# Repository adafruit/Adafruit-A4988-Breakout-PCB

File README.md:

## Adafruit A4988 Stepper Motor Driver Breakout Board PCB

<a href="http://www.adafruit.com/products/6109"><br/>
Click here to purchase one from the Adafruit shop</a>

PCB files for the Adafruit A4988 Stepper Motor Driver Breakout Board. 

Format is EagleCAD schematic and board layout
* https://www.adafruit.com/product/6109

### Description

Stepper motors are used for CNC machines, 3D printers, and whenever else one needs precise, powerful motion. But to get good behavior from steppers you need a motor driver chip that can provide high bursts of current, and for smooth motion, be able to PWM that current for microstepping support. You can DIY this with a lot of timers, a microcontroller and an  H-Bridge chip - or you could take the easy way out and use an Adafruit A4988 Stepper Motor Driver Breakout Board which makes controlling stepper motors easy-breezy.

All you need is two output pins, no timers, PWM or real-time microcontroller. Set the DIRection pin high or low to set the spin orientation. Then toggle the STEP pin to take one step or microstep at a time. You can set whether you want to go fast with single-step mode or improve the motion precise with 1/4, 1/8 or 1/16 microstepping per STEP toggle. By default the driver is set to 1/16 microstep mode, you can change it by tying the MS1/MS2/MS3 pins low, either with jumpers or with 3 more output pins. The step/microstep mode can even be adjusted on the fly! LEDs on the DIR and STEP pins let you get visual feedback of your motor signal.

The Allegro A4988 is a popular driver chip, with small breakout boards used in many 3D printers. Those breakouts are great for plugging into motherboards, but are a little tough to use for prototyping. Our version comes with terminal blocks for the motor power and stepper wires, plus nicely labeled pins for control and mounting holes.

We fabricated the board with 2 oz copper to give it a hand with the 2A-max current that this driver can handle. To use the current limiting capability, twist the onboard potentiometer: when all the way to the right we can get to up to 2A max. Note that the higher the currents will heat up both the motor driver and stepper so you may need to add heatsinking to the chip. We don't include a heatsink but you can get a tall ~80ºC/W or short ~90ºC/W heatsink to attach on top.

Features:

* Allegro A4988 DMOS microstepping driver with translator and overcurrent protection
* Motor voltage from 8V to 35VDC
* Vdd/Logic voltage from 3V to 5V, use with anything from an Arduino-compatible or ESP32 to Raspberry Pi other Single Board Computer
* Terminal screw block connections for easy VMotor power and 4-wire bi-polar stepper motor connection with 26-20AWG slots, 2.54mm / 0.1" spacing
* Control steppers using only two pins: DIRection and STEP
* Defaults to 1/16 microstep mode, change by grounding MS1/MS2/MS3 pins (see A4988 datasheet for pin configuration)
* Red and Green LEDs on DIR signal to let you know forward or backward motion
* Yellow LED on STEP to let you know that motor driver is being moved
* Sleep, Reset and Enable control lines for low power / deactivation
* Potentiometer to set current limiting, up to 2A
* 22uF 50V electrolytic capacitor on motor power
* 2 Oz copper for better current carrying and heatsinking
* Four mounting holes

Comes as one assembled and tested breakout plus a small strip of header. You'll need to do some light soldering to attach the header onto the breakout PCB. Microcontroller, motors, and power supply not included. You will need some sort of driver board that will toggle the DIR/STEP pins for you.

### License

Adafruit invests time and resources providing this open source design, please support Adafruit and open-source hardware by purchasing products from [Adafruit](https://www.adafruit.com)!

Designed by Limor Fried/Ladyada for Adafruit Industries.

Creative Commons Attribution/Share-Alike, all text above must be included in any redistribution. 
See license.txt for additional details.

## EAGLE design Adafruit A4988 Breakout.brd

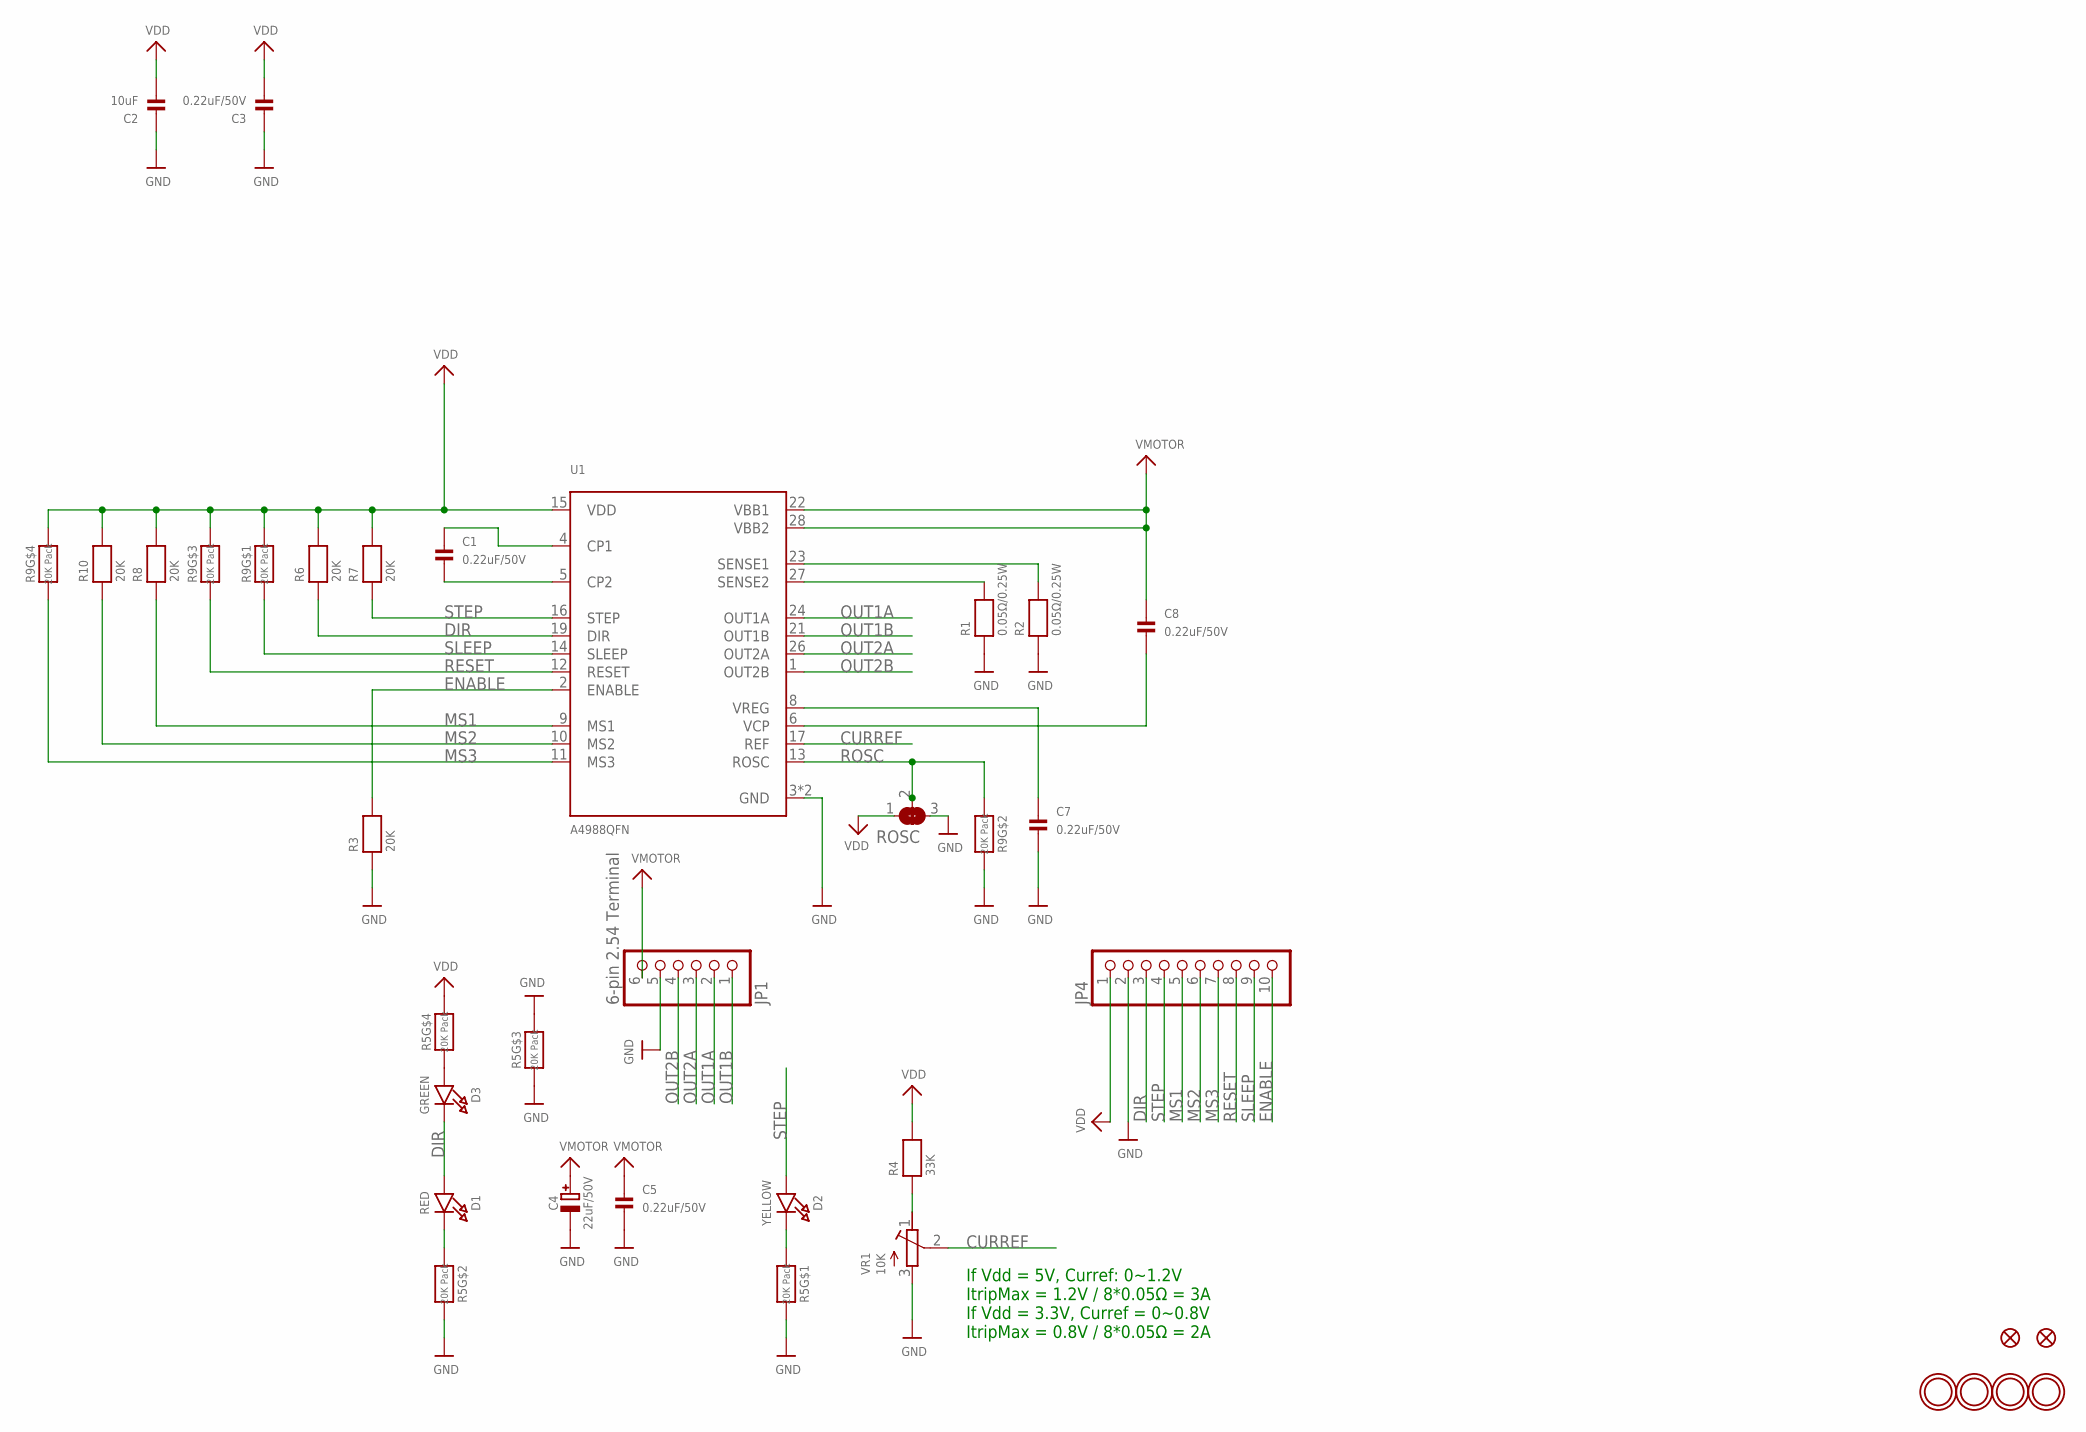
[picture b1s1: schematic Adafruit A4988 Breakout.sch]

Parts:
C1, C3, C5, C7, C8: 0.22uF/50V; 0603-NO
C2: 10uF; 0805-NO
C4: 22uF/50V; PANASONIC_C
D1: RED; CHIPLED_0603_NOOUTLINE
D2: YELLOW; CHIPLED_0603_NOOUTLINE
D3: GREEN; CHIPLED_0603_NOOUTLINE
JP1: 6-pin 2.54 Terminal; 1X06_2.54MMTERMINAL
JP4: HEADER-1X1070MIL; 1X10_ROUND70
R1, R2: 0.05Ω/0.25W; 0603-NO
R3, R6, R7, R8, R10: 20K; 0603-NO
R4: 33K; 0603-NO
R5, R9: 20K Pack; RESPACK_4X0603
ROSC: SOLDERJUMPER_2WAY; SOLDERJUMPER_2WAY_OPEN_NOPASTE
U1: A4988QFN; QFN28_5MM
U$10, U$11: FIDUCIAL_0.5MM
U$18, U$22, U$26, U$27: MOUNTINGHOLE2.0; MOUNTINGHOLE_2.0_PLATED
VR1: 10K; RTRIM3314J

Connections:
CURREF: U1.17 (REF), VR1.2 (S)
DIR: D1.A, D3.C, JP4.3, R6.1, U1.19 (DIR)
ENABLE: JP4.10, R3.2, U1.2 (ENABLE)
GND: C2.1, C3.1, C4.-, C5.2, C7.2, JP1.5, JP4.2, R1.1, R2.1, R3.1, R5.3 (1), R5.6 (2), R5.7 (2), R5.8 (2), R9.7 (2), ROSC.3, U1.3 (GND), U1.THERMAL (GND), VR1.3 (A)
MS1: JP4.5, R8.1, U1.9 (MS1)
MS2: JP4.6, R10.1, U1.10 (MS2)
MS3: JP4.7, R9.4 (1), U1.11 (MS3)
unnamed: D2.C, R5.1
unnamed: C1.1, U1.4 (CP1)
unnamed: C1.2, U1.5 (CP2)
unnamed: C8.2, U1.6 (VCP)
unnamed: R1.2, U1.27 (SENSE2)
unnamed: R2.2, U1.23 (SENSE1)
unnamed: C7.1, U1.8 (VREG)
unnamed: D1.C, R5.2 (1)
unnamed: R4.1, VR1.1 (E)
unnamed: D3.A, R5.4 (1)
OUT1A: JP1.2, U1.24 (OUT1A)
OUT1B: JP1.1, U1.21 (OUT1B)
OUT2A: JP1.3, U1.26 (OUT2A)
OUT2B: JP1.4, U1.1 (OUT2B)
RESET: JP4.8, R9.3 (1), U1.12 (RESET)
ROSC: R9.2 (1), ROSC.2, U1.13 (ROSC)
SLEEP: JP4.9, R9.1, U1.14 (SLEEP)
STEP: D2.A, JP4.4, R7.1, U1.16 (STEP)
VDD: C2.2, C3.2, JP4.1, R4.2, R5.5 (2), R6.2, R7.2, R8.2, R9.5 (2), R9.6 (2), R9.8 (2), R10.2, ROSC.1, U1.15 (VDD)
VMOTOR: C4.+, C5.1, C8.1, JP1.6, U1.22 (VBB1), U1.28 (VBB2)

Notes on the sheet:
If Vdd = 5V, Curref: 0~1.2V ItripMax = 1.2V / 8*0.05Ω = 3A If Vdd = 3.3V, Curref = 0~0.8V ItripMax = 0.8V / 8*0.05Ω = 2A

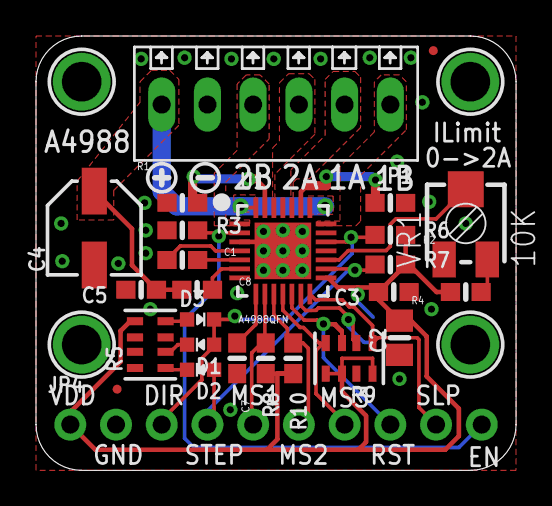
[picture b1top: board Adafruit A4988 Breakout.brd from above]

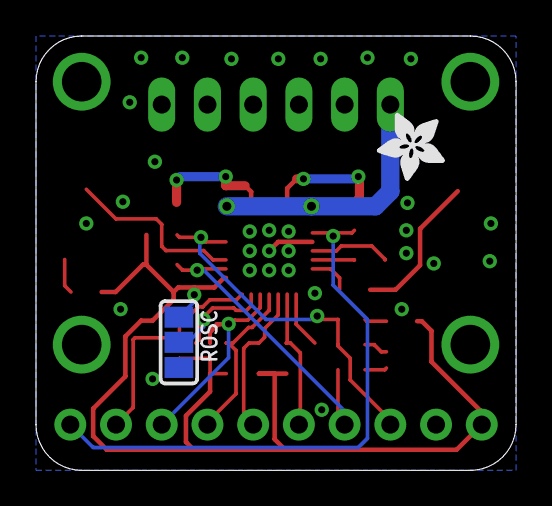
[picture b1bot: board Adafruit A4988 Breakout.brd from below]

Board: 2 copper layers, 26.7 x 24.1 mm, 34 parts (2 on the bottom side), 27 nets.

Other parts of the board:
U$7: SYMBOL_PLUS
U$8: SYMBOL_MINUS
U$24: ADAFRUIT_3.5MM

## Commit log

2024-12-13 cookiecutter
